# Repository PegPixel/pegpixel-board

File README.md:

# pegpixel-arduino

This contains the code that receives updates via Bluetooth

* parses the data
* updates the LEDs

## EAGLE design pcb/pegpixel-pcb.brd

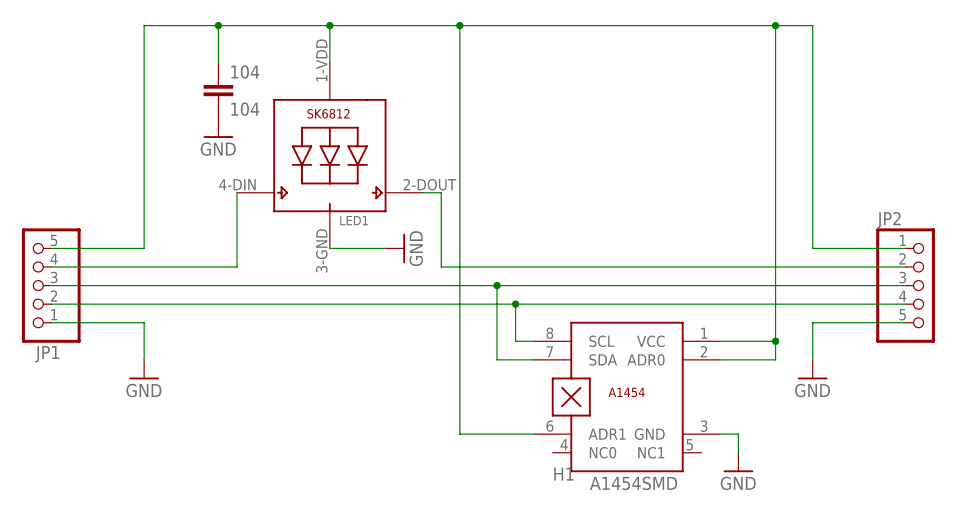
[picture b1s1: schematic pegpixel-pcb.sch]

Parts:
104: 104; C0805
H1: A1454SMD; TSSOP8
JP1, JP2: PINHD-1X5/90; 1X05/90
LED1: SK6812_5050; LED5050

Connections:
DIN: JP1.4, LED1.4-DIN (DI)
DOUT: JP2.2, LED1.2-DOUT (DO)
GND: 104.2, H1.3 (GND), JP1.1, JP2.5, LED1.3-GND (GND)
SCL: H1.8 (SCL), JP1.2, JP2.4
SDA: H1.7 (SDA), JP1.3, JP2.3
VCC: 104.1, H1.1 (VCC), H1.2 (ADR0), H1.6 (ADR1), JP1.5, JP2.1, LED1.1-VDD (VDD)

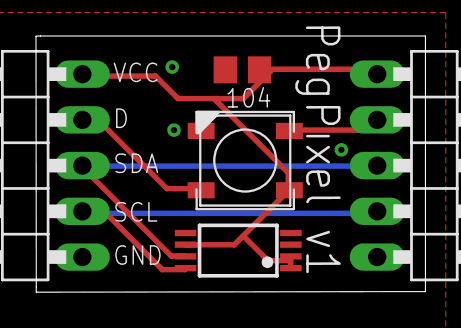
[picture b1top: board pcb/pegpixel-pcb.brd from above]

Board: 2 copper layers, 21.6 x 14.2 mm, 5 parts (0 on the bottom side), 6 nets.

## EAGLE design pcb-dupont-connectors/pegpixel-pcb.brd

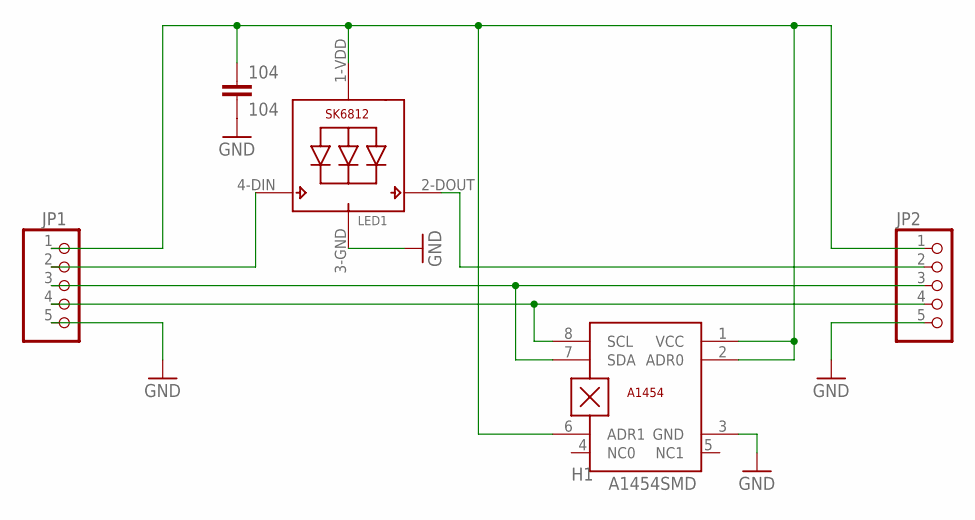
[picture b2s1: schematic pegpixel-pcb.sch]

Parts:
104: 104; C0805
H1: A1454SMD; TSSOP8
JP1, JP2: PINHD-1X5/90; 1X05/90
LED1: SK6812_5050; LED5050

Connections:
DIN: JP1.2, LED1.4-DIN (DI)
DOUT: JP2.2, LED1.2-DOUT (DO)
GND: 104.2, H1.3 (GND), JP1.5, JP2.5, LED1.3-GND (GND)
SCL: H1.8 (SCL), JP1.4, JP2.4
SDA: H1.7 (SDA), JP1.3, JP2.3
VCC: 104.1, H1.1 (VCC), H1.2 (ADR0), H1.6 (ADR1), JP1.1, JP2.1, LED1.1-VDD (VDD)

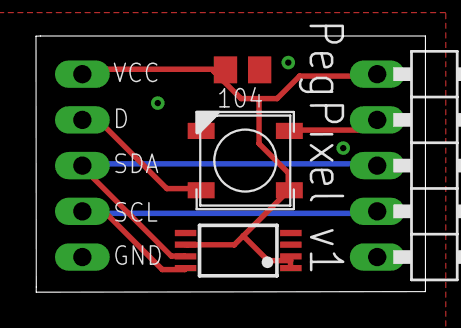
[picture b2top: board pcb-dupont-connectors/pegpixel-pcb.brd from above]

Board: 2 copper layers, 21.6 x 14.2 mm, 5 parts (1 on the bottom side), 6 nets.

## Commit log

2018-09-13 Initial Commit: Read from BT-Serial and parse JSON (each object in array)
2018-09-13 Json-Preparsing: Ignore commata separating objects
2018-09-13 First version, where I can control LEDs via Smartphone ... lots of issues, though
2018-09-14 Add read single char
2018-09-14 Finally, a reliable, quick version!
2018-09-14 Replace usage of char-array with string
2018-09-14 Convert incoming array-indices to pixel-index
2018-09-14 Introduce struct for parsed pixel + use static json parser
2018-09-14 Remove debug-infos
2018-09-14 refactor for readability
2018-09-16 Read RGB from Bluetooth and paint pixels
2018-09-16 Receive CSV-based info (seems buggy)
2018-09-16 Wohoow, the pixels light up in the correct color :DD
2018-10-10 Add pulse-function
2018-10-12 write messages to array to try to prevent overflow of buffer (not working)
2018-10-13 draw a bouncing ball on matrix
2018-10-17 Add parsing for simple format
2018-10-17 Remove debugging - problem lies within NeoPixel they disable interrupts, which messes with the BT-reption
2018-10-22 start peg-indices with 0 (instead of 1)
2018-10-23 move bouncing ball code to separate file
2018-10-23 move "pulse red" to separate file
2018-10-23 rename files from .c to .ino
2018-10-23 add license
2018-10-23 misc code cleanup
2018-11-07 Migrate code to ESP32: - Switch Bluetooth-lib - Switch LED-lib
2018-11-07 add .vscode/* to .gitignore
2018-11-07 send gamma-corrected colors to LEDs
2018-11-08 cleanup includes
2018-11-08 update pegpixel-board bluetooth-name
2018-11-08 slow down pulse of active LEDs
2018-11-12 rename pegpixel.ino to pegpixel-board.ino
2018-11-15 add hallsensor.ino as an example to read magnetic field from A1454
2018-11-25 add code to write an A1454's I2C address
2018-11-28 only allow 1 .ino file, change default i2c address of A1454 to 0x00
2018-12-08 use hall effect read from A1454 via i2c to switch off pixels
2018-12-09 use neotimer instead of delay
2018-12-13 add very first version of PCB as EAGLE schematic
2018-12-13 update PCB with A1454
2019-01-04 add first pcb layout
2019-01-12 Add second capacitor to schema
2019-01-12 Add second capacitor to schema #2
2019-01-12 Add pcb-version with pin-headers
2019-01-12 Remove second capacitor
2019-01-12 adjust labels on pcb
2019-01-12 pcb-design: add missing GRND-via
2019-01-12 pcb-design: Replace i with dotless version in PegPixel
2019-01-13 mirror and turn input pin header to place it on top layer
2019-01-14 pcb-design: move via away from lane
2019-01-14 pcb-design: delete design with solder-points
2019-01-14 pcb-design: reposition label
2019-02-24 add two new sensors to test-rig
2019-07-31 add scan for pegpixels at setup
